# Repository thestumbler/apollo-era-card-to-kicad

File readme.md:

# Apollo-Era-Card-RevEng

See the accompanying Hackaday writeup about this schematic project:

[https://hackaday.com/2024/11/25/apollo-era-pcb-reverse-engineering-to-kicad](
https://hackaday.com/2024/11/25/apollo-era-pcb-reverse-engineering-to-kicad)

This repo documents additional explorations into the reverse engineering
effort of an Apollo-era printed circuit board assemly that Skyhawkson
obtained earlier this year. See his project at the [original
repo](https://github.com/Skyhawkson/Apollo-Era-Card-RevEng/tree/main).

Note: I planned to submit this as a pull request to Skyhawkson's
repository. But I ran into trouble with git and spaces in filenames, a
problem I haven't seen before. 

### Best Guess

This is an interface board for reading sensors such as strain gauges. 
It features a precision voltage source to excite the bridge. It also 
has a differential amplifier to scale up the sensor voltage and
proportionally drive an output load. The output stage has an enable pin,
suggesting that multiple card outputs may be multiplexed into one analog
to digital circuit card. That makes sense, since scanning through a
bunch of sensors over and over again makes sense in the context of
running through test sequences.

If there are any updates based on comments from Hackaday readers or
anyone here in GitHub, or just random new insights, I will update the
repository as necessary.

### Schematic

Schematic [(PDF)](eda-logical/logical-sch.pdf)

### Original Readme

Reverse Engineering an Apollo-Era Circuit Card

https://github.com/Skyhawkson/Apollo-Era-Card-RevEng/tree/main

[Writeup on hackaday.io](https://hackaday.io/project/194704-reverse-engineering-an-apollo-era-circuit-card)

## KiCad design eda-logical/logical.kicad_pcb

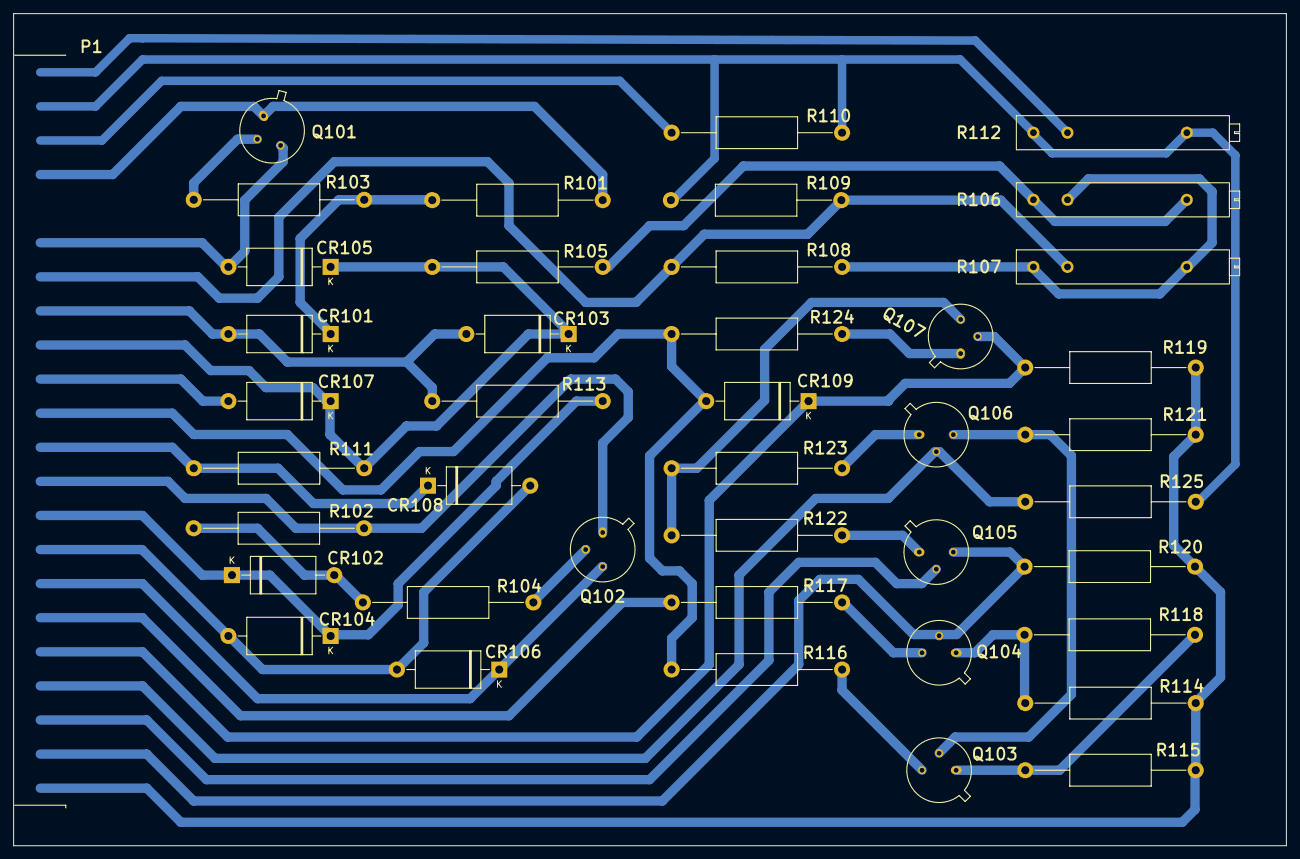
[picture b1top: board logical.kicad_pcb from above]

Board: 2 copper layers, 189.7 x 124.0 mm, 42 parts (0 on the bottom side), 36 nets.

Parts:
CR101, CR102, CR109: 1N754A; D_DO-27_P15.24mm_Horizontal
CR103, CR104: 1N458; D_DO-27_P15.24mm_Horizontal
CR105, CR106, CR107: 1N4003; D_DO-27_P15.24mm_Horizontal
CR108: 1N2625; D_DO-27_P15.24mm_Horizontal
P1: IO_PLUG_M22; EDGE_22_SINGLE_p0.156
Q101: 2N1305; TO-5-3
Q102: 2N1304; TO-5-3
Q103, Q104: 2N1038; TO-5-3
Q105, Q106, Q107: 2N697; TO-5-3
R101, R102: 1000; R_Axial_DIN0414_L11.9mm_D4.5mm_P25.40mm_Horizontal
R103, R104: 2000; R_Axial_DIN0414_L11.9mm_D4.5mm_P25.40mm_Horizontal
R105: 450 1%; R_Axial_DIN0414_L11.9mm_D4.5mm_P25.40mm_Horizontal
R106: 500; Potentiometer_Bourns_224P
R107: 100; Potentiometer_Bourns_224P
R108: 39 5%; R_Axial_DIN0414_L11.9mm_D4.5mm_P25.40mm_Horizontal
R109: 2500 1%; R_Axial_DIN0414_L11.9mm_D4.5mm_P25.40mm_Horizontal
R110: 500 1%; R_Axial_DIN0414_L11.9mm_D4.5mm_P25.40mm_Horizontal
R111: 1500; R_Axial_DIN0414_L11.9mm_D4.5mm_P25.40mm_Horizontal
R112: 10; Potentiometer_Bourns_224P
R113: 2.7K 3%; R_Axial_DIN0414_L11.9mm_D4.5mm_P25.40mm_Horizontal
R114, R115: 150; R_Axial_DIN0414_L11.9mm_D4.5mm_P25.40mm_Horizontal
R116, R117: 250; R_Axial_DIN0414_L11.9mm_D4.5mm_P25.40mm_Horizontal
R118, R123: 10; R_Axial_DIN0414_L11.9mm_D4.5mm_P25.40mm_Horizontal
R119: 1.5K; R_Axial_DIN0414_L11.9mm_D4.5mm_P25.40mm_Horizontal
R120, R121: 2.5K 3%; R_Axial_DIN0414_L11.9mm_D4.5mm_P25.40mm_Horizontal
R122: 50; R_Axial_DIN0414_L11.9mm_D4.5mm_P25.40mm_Horizontal
R124: 1600; R_Axial_DIN0414_L11.9mm_D4.5mm_P25.40mm_Horizontal
R125: 0.1?; R_Axial_DIN0414_L11.9mm_D4.5mm_P25.40mm_Horizontal

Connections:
/NET22: Q101.2 (B), R103.2
/NET23: R105.1, R106.2, R106.3
/NET24: R106.1, R107.2, R107.3, R108.1
/NET25: CR101.1 (K), R101.2, R103.1
/NET26: CR102.2 (A), R102.2, R104.2
/NET27: Q102.2 (B), R104.1
/NET28: Q107.3 (C), R122.2, R123.2
/NET29: Q107.1 (E), R124.1
/NET30: Q106.1 (E), R123.1
/NET31: Q105.1 (E), R122.1
/NET32: Q104.3 (C), R117.1
/NET33: Q103.2 (B), Q106.3 (C), R121.2
/NET34: Q104.1 (E), R114.2, R118.2
/NET35: Q103.3 (C), R116.1
/NET36: Q103.1 (E), R115.2, R118.1
NET1: P1.1, R112.1
NET2: P1.2, R109.2, R110.1, R112.2, R112.3, R125.1
NET3: P1.3, R110.2
NET4: P1.4, Q101.1 (E), R101.1
NET5: CR105.2 (A), P1.6, Q101.3 (C)
NET6: P1.7, R107.1, R108.2, R109.1
NET7: CR101.2 (A), CR103.2 (A), P1.8, R113.2
NET8: CR103.1 (K), CR105.1 (K), CR107.1 (K), P1.9, R105.2, R111.1
NET9: CR107.2 (A), P1.10
NET10: CR109.2 (A), P1.11, R116.2, R124.2
NET11: CR108.1 (K), P1.12, R111.2
NET12: P1.13, Q102.1 (E), R102.1
NET13: CR102.1 (K), CR104.1 (K), P1.14, R113.1
NET14: CR104.2 (A), CR106.2 (A), CR108.2 (A), P1.15
NET15: CR106.1 (K), P1.16, Q102.3 (C)
NET16: P1.17, R117.2
NET17: CR109.1 (K), P1.18, Q107.2 (B), R119.2
NET18: P1.19, Q106.2 (B), R125.2
NET19: P1.20, Q105.2 (B)
NET20: P1.21, Q104.2 (B), Q105.3 (C), R120.2
NET21: P1.22, R114.1, R115.1, R119.1, R120.1, R121.1

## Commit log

2024-11-17 initial release, preliminary
2024-11-17 removed large PDF files
2024-11-17 fixed readme link image
2024-11-25 minor cleanups and tweaks
2024-11-26 updated readme, added 1n262x data sheet
